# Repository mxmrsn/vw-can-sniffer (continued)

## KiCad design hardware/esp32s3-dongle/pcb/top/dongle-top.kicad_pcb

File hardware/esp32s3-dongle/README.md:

# OBD dongle (v0.4.0, laid out on a temporary outline)

| Path | What it is |
|---|---|
| [`pcb/`](pcb/README.md) | Schematics for both boards and the scripts that generate them |
| [`firmware/`](firmware/README.md) | ESP-IDF firmware: the shared core plus the TJA1043 modes and switching itself off |
| [`docs/architecture.md`](docs/architecture.md) | The two-board stack behind a J1962 plug: partitioning, power and sleep, the board-to-board connector, the mechanical interface with the enclosure, and what is still to verify |

The low-profile version of the [XIAO board](../xiao-esp32s3/README.md): same firmware core, protocol and tools,
plugged straight into the OBD port, and switching itself off when the car is parked. **The schematics are drawn**
and ERC clean, and both boards are routed (0 DRC errors) on a temporary outline, with STEP files for the
enclosure. The real outline follows the enclosure.

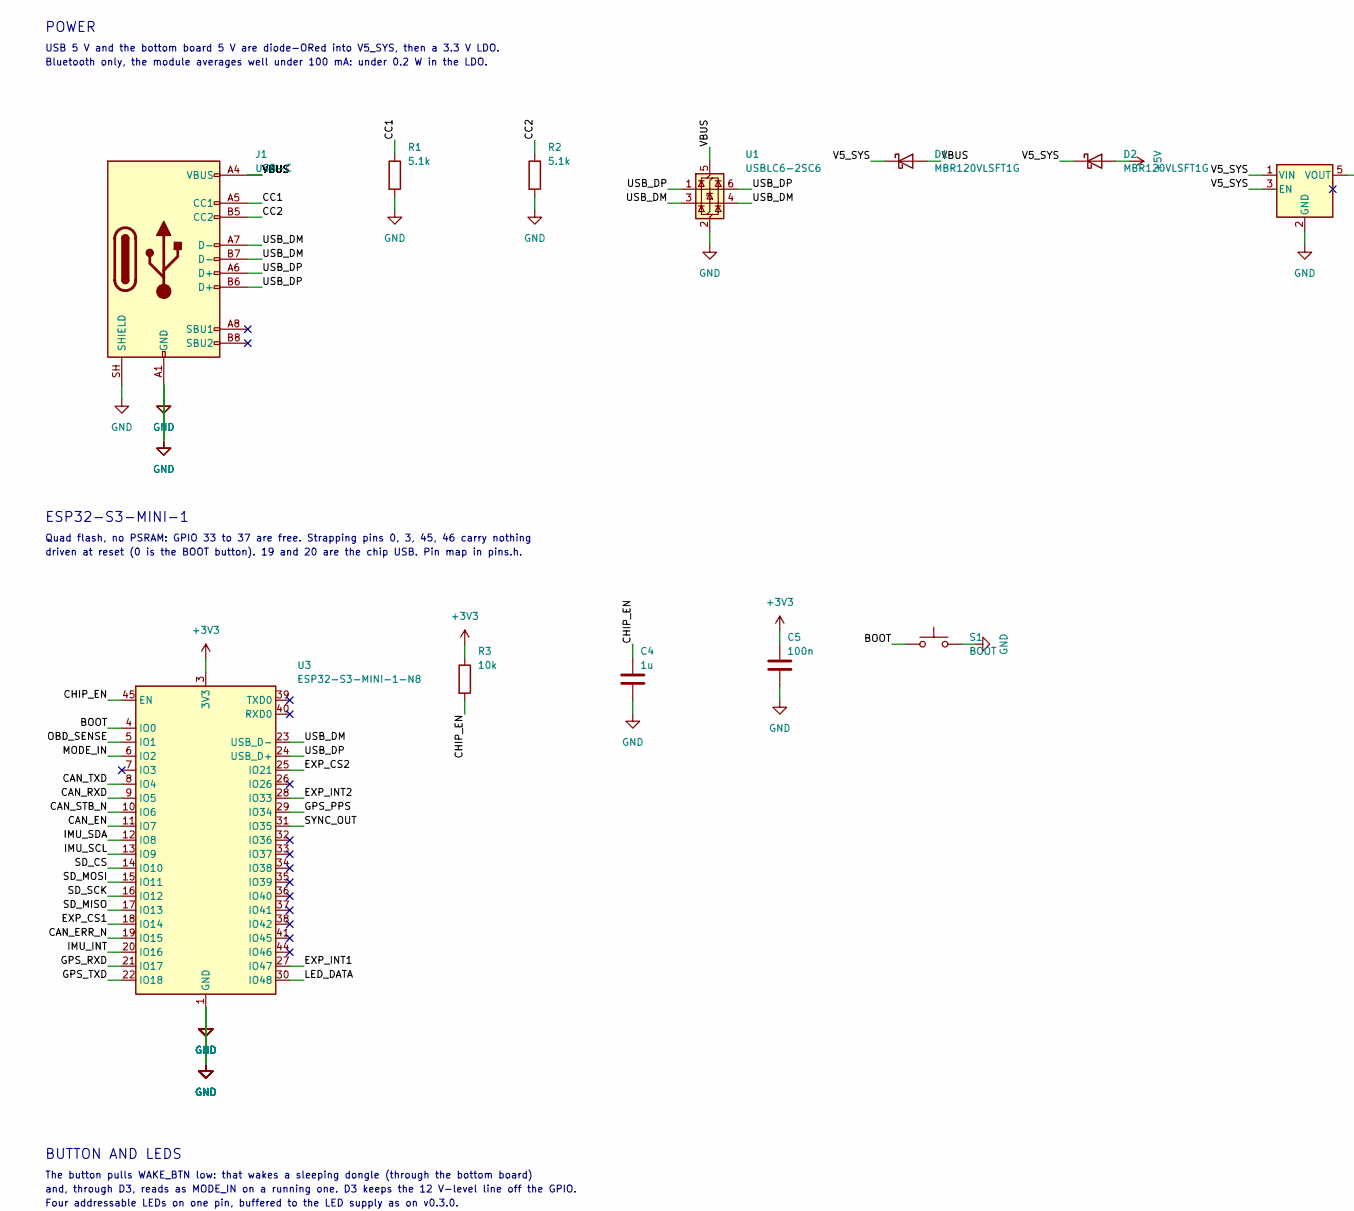
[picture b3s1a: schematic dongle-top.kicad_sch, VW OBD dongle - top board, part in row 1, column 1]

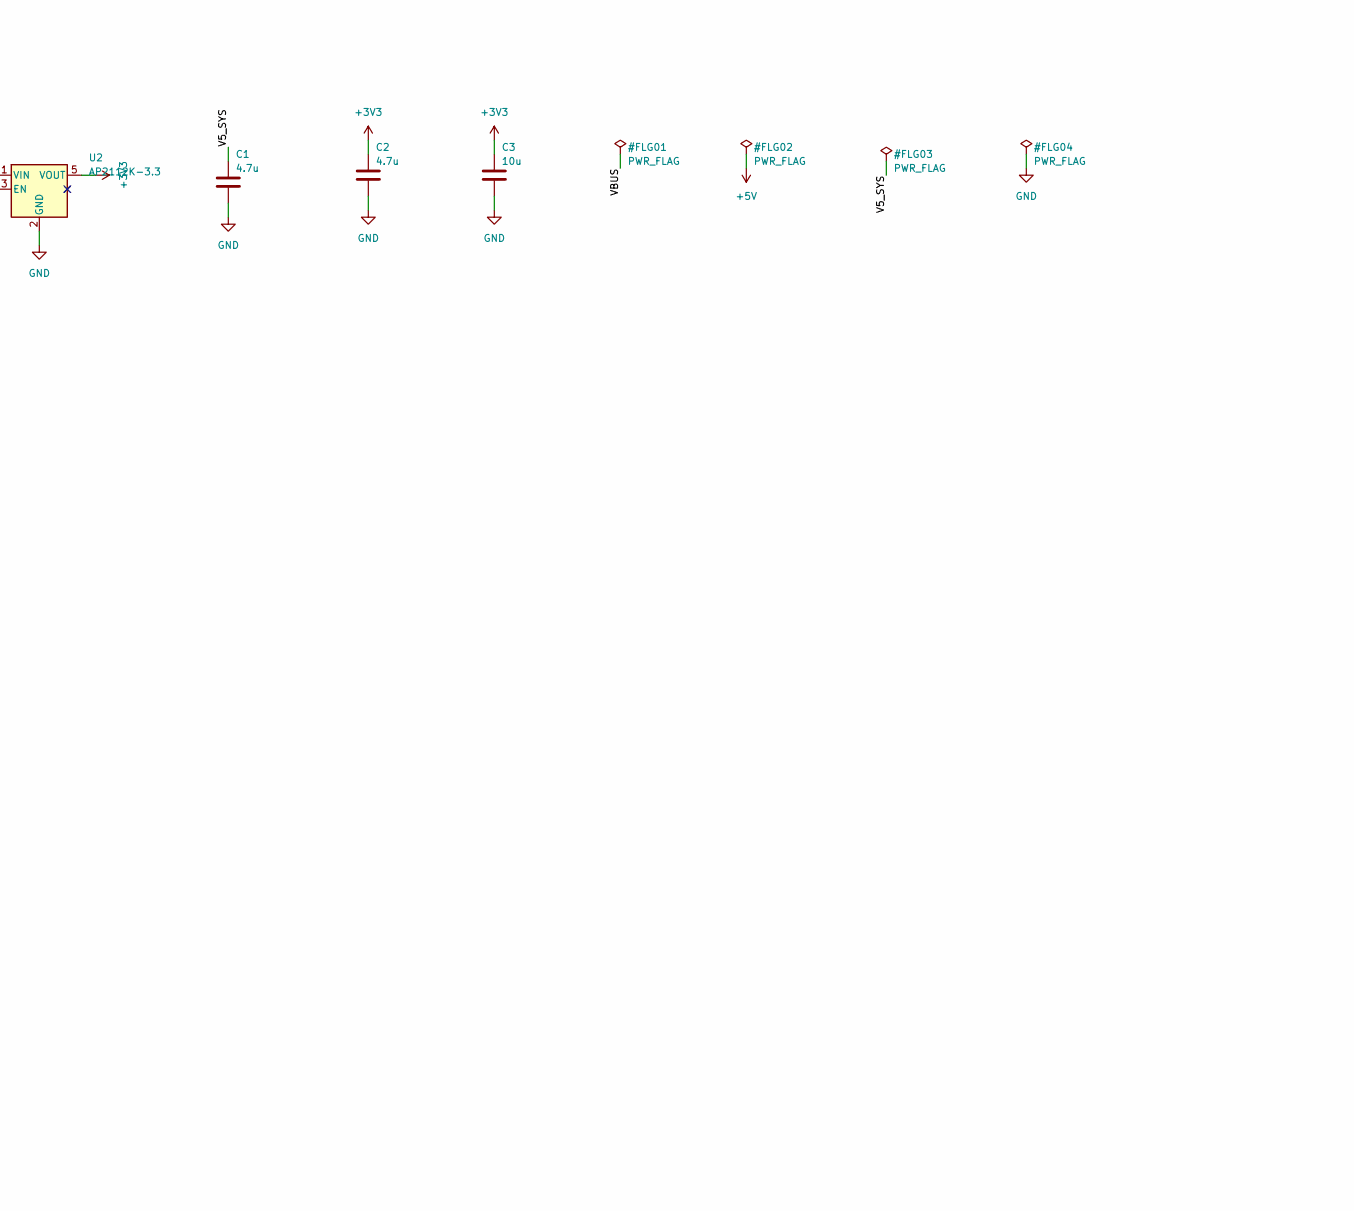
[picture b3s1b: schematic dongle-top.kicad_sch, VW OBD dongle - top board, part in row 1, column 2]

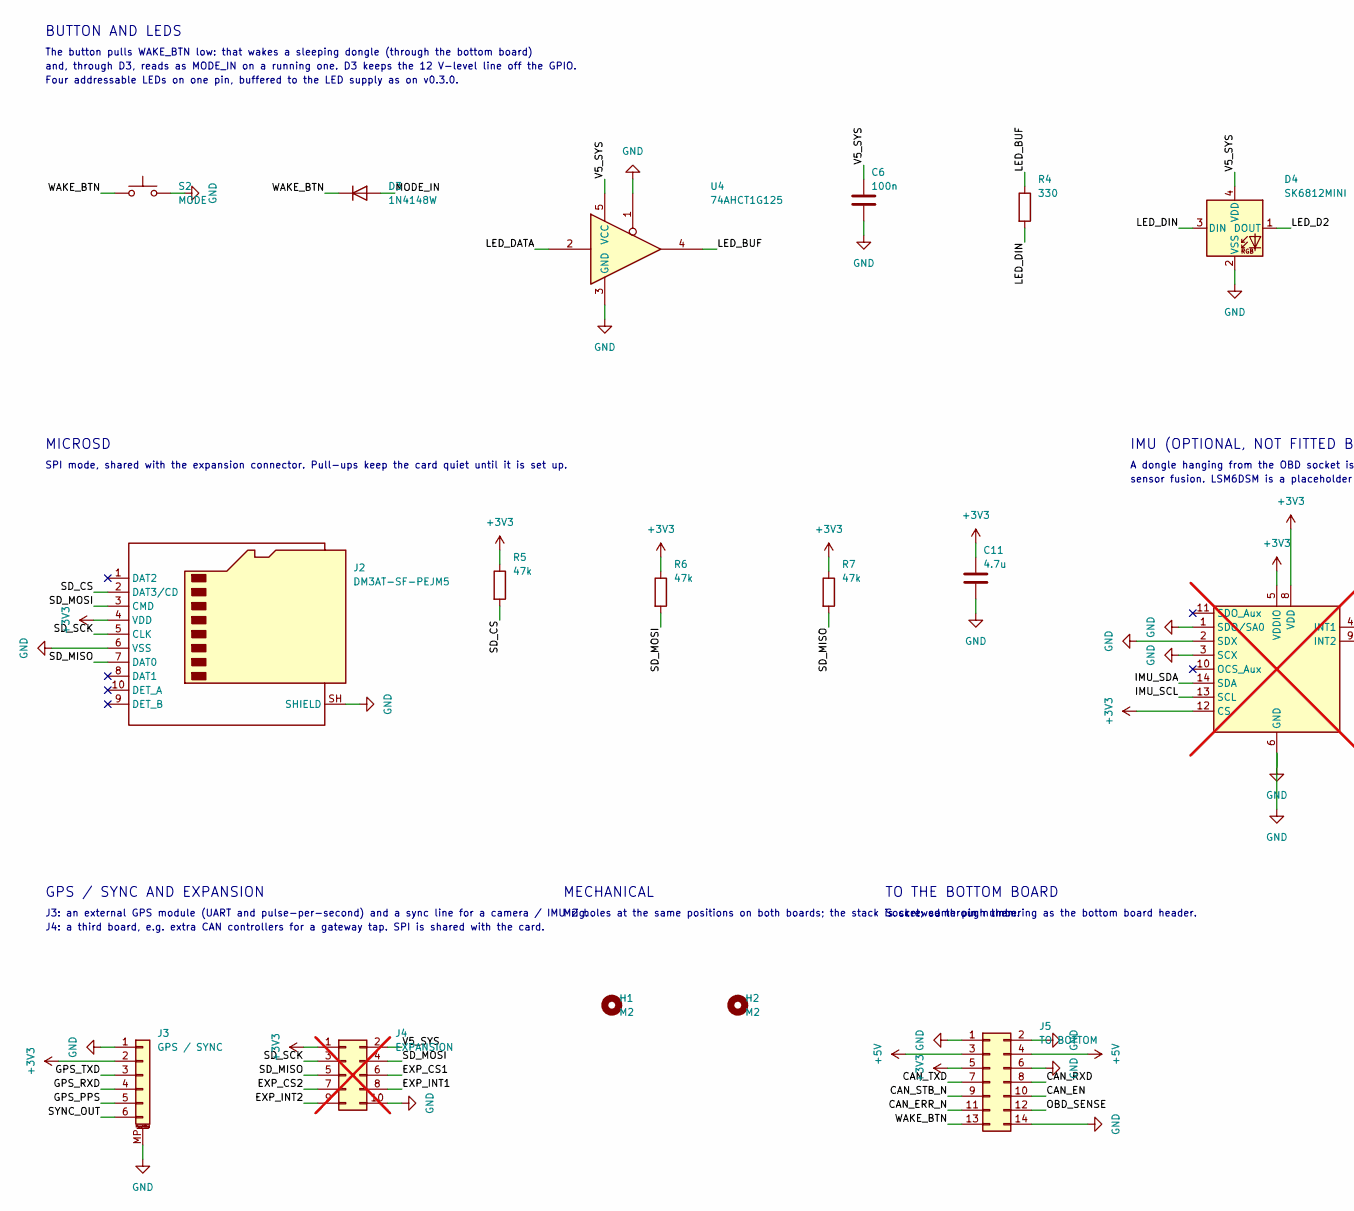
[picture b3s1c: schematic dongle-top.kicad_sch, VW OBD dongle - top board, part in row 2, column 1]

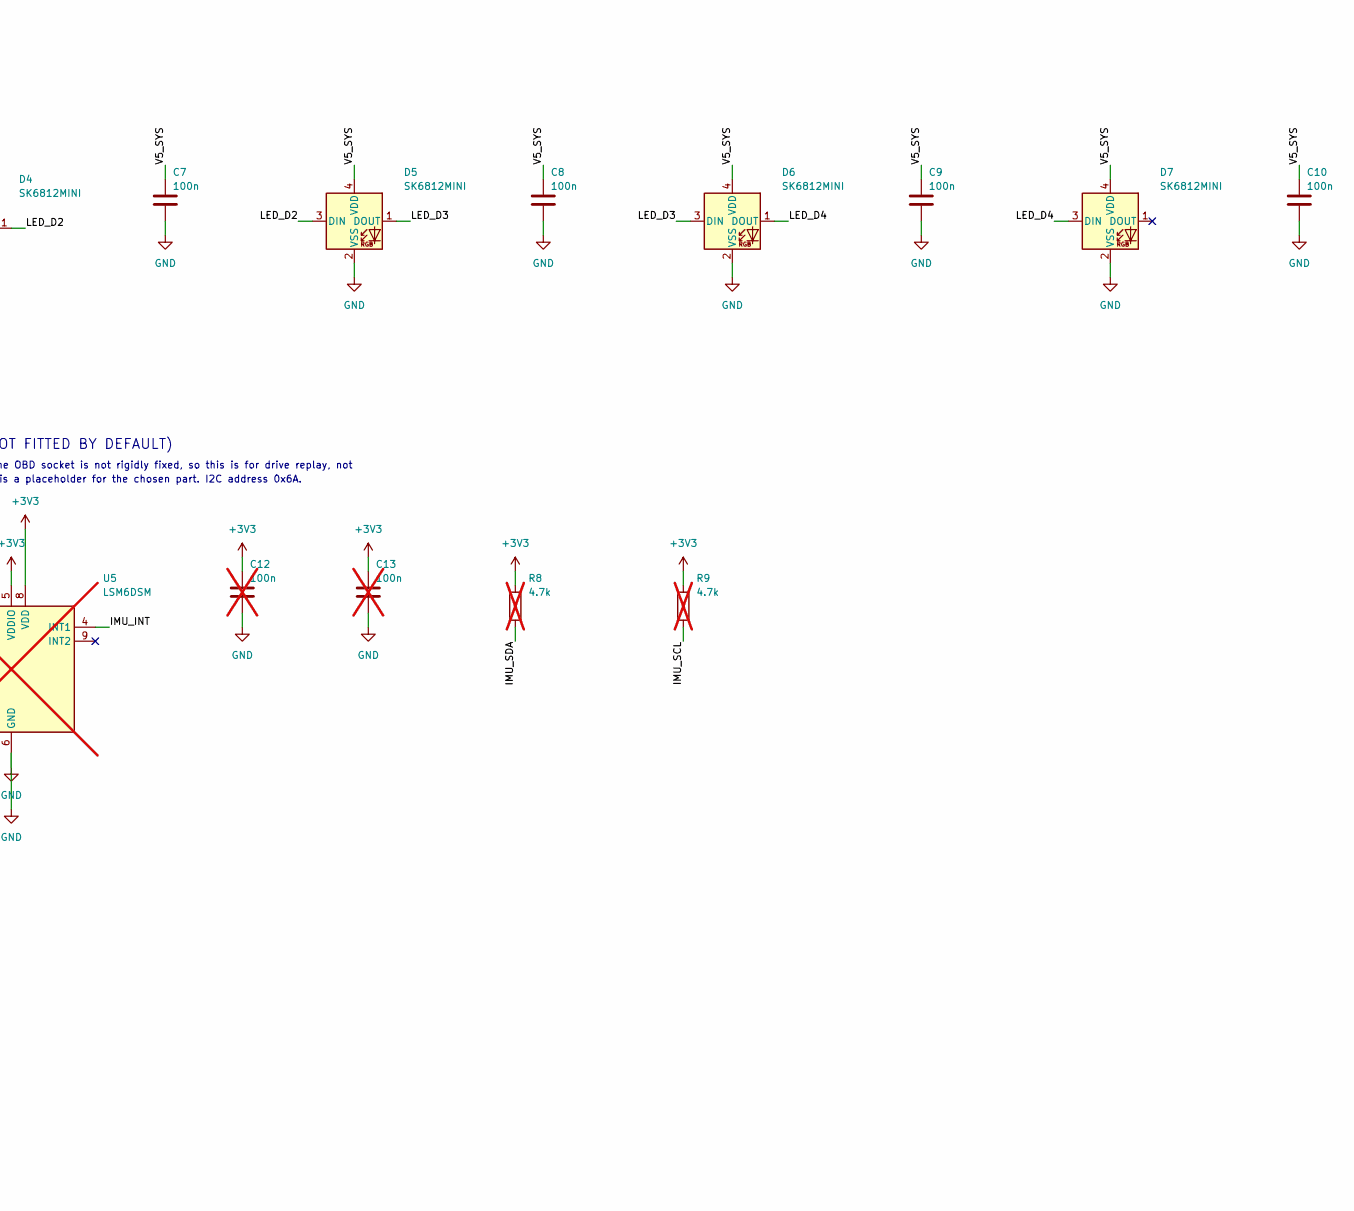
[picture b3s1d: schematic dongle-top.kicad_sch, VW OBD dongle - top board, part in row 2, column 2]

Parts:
C1, C2, C11: 4.7u; C_0603_1608Metric; MPN CC0603KRX5R7BB475; DigiKey 311-1785-1-ND
C3: 10u; C_0805_2012Metric; MPN GMC21X5R106K50NT; DigiKey 4713-GMC21X5R106K50NTCT-ND
C4: 1u; C_0603_1608Metric; MPN CL10A105KB8NNNC
C5, C6, C7, C8, C9, C10: 100n; C_0603_1608Metric; MPN CC0603KRX7R9BB104; DigiKey 311-1344-1-ND
C12, C13: 100n; C_0603_1608Metric; MPN CC0603KRX7R9BB104; DigiKey 311-1344-1-ND; not fitted
D1, D2: MBR120VLSFT1G; D_SOD-123F; MPN MBR120VLSFT1G; DigiKey MBR120VLSFT1GOSCT-ND
D3: 1N4148W; D_SOD-123; MPN 1N4148W-7-F
D4, D5, D6, D7: SK6812MINI; LED_SK6812MINI_PLCC4_3.5x3.5mm_P1.75mm; MPN SK6812MINI (to verify)
H1, H2: M2; MountingHole_2.2mm_M2
J1: USB-C; USB_C_Receptacle_GCT_USB4105-xx-A_16P_TopMnt_Horizontal; MPN USB4105-GF-A
J2: DM3AT-SF-PEJM5; microSD_HC_Hirose_DM3AT-SF-PEJM5; MPN DM3AT-SF-PEJM5; DigiKey HR1964CT-ND
J3: GPS / SYNC; JST_GH_SM06B-GHS-TB_1x06-1MP_P1.25mm_Horizontal; MPN SM06B-GHS-TB(LF)(SN)
J4: EXPANSION; PinHeader_2x05_P1.27mm_Vertical_SMD; not fitted
J5: TO BOTTOM; PinSocket_2x07_P1.27mm_Vertical_SMD
R1, R2: 5.1k; R_0603_1608Metric; MPN CRCW06035K10FKEA
R3: 10k; R_0603_1608Metric; MPN CRCW060310K0FKEA; DigiKey 541-10.0KHCT-ND
R4: 330; R_0603_1608Metric; MPN CRCW0603330RFKEA; DigiKey 541-330HCT-ND
R5, R6, R7: 47k; R_0603_1608Metric; MPN CRCW060347K0FKEA
R8, R9: 4.7k; R_0603_1608Metric; MPN CRCW06034K70FKEA; not fitted
S1: BOOT; SW_SPST_PTS810; MPN PTS810 SJM 250 SMTR LFS
S2: MODE; SW_SPST_PTS810; MPN PTS810 SJM 250 SMTR LFS
U1: USBLC6-2SC6; SOT-23-6; MPN USBLC6-2SC6
U2: AP2112K-3.3; SOT-23-5; MPN AP2112K-3.3TRG1
U3: ESP32-S3-MINI-1-N8; ESP32-S2-MINI-1; MPN ESP32-S3-MINI-1-N8
U4: 74AHCT1G125; SOT-23-5; MPN SN74AHCT1G125DBVR
U5: LSM6DSM; LGA-14_3x2.5mm_P0.5mm_LayoutBorder3x4y; MPN LSM6DSM (placeholder); not fitted

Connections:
+3V3: C2.1, C3.1, C5.1, C11.1, C12.1, C13.1, J2.4 (VDD), J3.2, J4.1, J5.5, R3.1, R5.1, R6.1, R7.1, R8.1, R9.1, U2.5 (VOUT), U3.3 (3V3), U5.5 (VDDIO), U5.8 (VDD), U5.12 (CS)
+5V: D2.2 (A), J5.3, J5.4
/BOOT: S1.1, U3.4 (IO0)
/CAN_EN: J5.10, U3.11 (IO7)
/CAN_ERR_N: J5.11, U3.19 (IO15)
/CAN_RXD: J5.8, U3.9 (IO5)
/CAN_STB_N: J5.9, U3.10 (IO6)
/CAN_TXD: J5.7, U3.8 (IO4)
/CC1: J1.A5 (CC1), R1.1
/CC2: J1.B5 (CC2), R2.1
/CHIP_EN: C4.1, R3.2, U3.45 (EN)
/EXP_CS1: J4.6, U3.18 (IO14)
/EXP_CS2: J4.7, U3.25 (IO21)
/EXP_INT1: J4.8, U3.27 (IO47)
/EXP_INT2: J4.9, U3.28 (IO33)
/GPS_PPS: J3.5, U3.29 (IO34)
/GPS_RXD: J3.4, U3.21 (IO17)
/GPS_TXD: J3.3, U3.22 (IO18)
/IMU_INT: U3.20 (IO16), U5.4 (INT1)
/IMU_SCL: R9.2, U3.13 (IO9), U5.13 (SCL)
/IMU_SDA: R8.2, U3.12 (IO8), U5.14 (SDA)
/LED_BUF: R4.1, U4.4
/LED_D2: D4.1 (DOUT), D5.3 (DIN)
/LED_D3: D5.1 (DOUT), D6.3 (DIN)
/LED_D4: D6.1 (DOUT), D7.3 (DIN)
/LED_DATA: U3.30 (IO48), U4.2
/LED_DIN: D4.3 (DIN), R4.2
/MODE_IN: D3.2 (A), U3.6 (IO2)
/OBD_SENSE: J5.12, U3.5 (IO1)
/SD_CS: J2.2 (DAT3/CD), R5.2, U3.14 (IO10)
/SD_MISO: J2.7 (DAT0), J4.5, R7.2, U3.17 (IO13)
/SD_MOSI: J2.3 (CMD), J4.4, R6.2, U3.15 (IO11)
/SD_SCK: J2.5 (CLK), J4.3, U3.16 (IO12)
/SYNC_OUT: J3.6, U3.31 (IO35)
/USB_DM: J1.A7 (D-), J1.B7 (D-), U1.3 (I/O2), U1.4 (I/O2), U3.23 (USB_D-)
/USB_DP: J1.A6 (D+), J1.B6 (D+), U1.1 (I/O1), U1.6 (I/O1), U3.24 (USB_D+)
/V5_SYS: C1.1, C6.1, C7.1, C8.1, C9.1, C10.1, D1.1 (K), D2.1 (K), D4.4 (VDD), D5.4 (VDD), D6.4 (VDD), D7.4 (VDD), J4.2, U2.1 (VIN), U2.3 (EN), U4.5 (VCC)
/VBUS: D1.2 (A), J1.A4 (VBUS), J1.A9 (VBUS), J1.B4 (VBUS), J1.B9 (VBUS), U1.5 (VBUS)
/WAKE_BTN: D3.1 (K), J5.13, S2.1
GND: C1.2, C2.2, C3.2, C4.2, C5.2, C6.2, C7.2, C8.2, C9.2, C10.2, C11.2, C12.2, C13.2, D4.2 (VSS), D5.2 (VSS), D6.2 (VSS), D7.2 (VSS), J1.A1 (GND), J1.A12 (GND), J1.B1 (GND), J1.B12 (GND), J1.SH (SHIELD), J2.6 (VSS), J2.SH (SHIELD), J3.1, J3.MP (MountPin), J4.10, J5.1, J5.2, J5.6, J5.14, R1.2, R2.2, S1.2, S2.2, U1.2 (GND), U2.2 (GND), U3.1 (GND), U3.2 (GND), U3.42 (GND), U3.43 (GND), U3.46 (GND), U3.47 (GND), U3.48 (GND), U3.49 (GND), U3.50 (GND), U3.51 (GND), U3.52 (GND), U3.53 (GND), U3.54 (GND), U3.55 (GND), U3.56 (GND), U3.57 (GND), U3.58 (GND), U3.59 (GND), U3.60 (GND), U3.61 (GND), U3.62 (GND), U3.63 (GND), U3.64 (GND), U3.65 (GND), U4.1, U4.3 (GND), U5.1 (SDO/SA0), U5.2 (SDX), U5.3 (SCX), U5.6 (GND), U5.7 (GND)

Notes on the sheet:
POWER
USB 5 V and the bottom board 5 V are diode-ORed into V5_SYS, then a 3.3 V LDO.
Bluetooth only, the module averages well under 100 mA: under 0.2 W in the LDO.
ESP32-S3-MINI-1
Quad flash, no PSRAM: GPIO 33 to 37 are free. Strapping pins 0, 3, 45, 46 carry nothing
driven at reset (0 is the BOOT button). 19 and 20 are the chip USB. Pin map in pins.h.
BUTTON AND LEDS
The button pulls WAKE_BTN low: that wakes a sleeping dongle (through the bottom board)
and, through D3, reads as MODE_IN on a running one. D3 keeps the 12 V-level line off the GPIO.
Four addressable LEDs on one pin, buffered to the LED supply as on v0.3.0.
MICROSD
SPI mode, shared with the expansion connector. Pull-ups keep the card quiet until it is set up.
IMU (OPTIONAL, NOT FITTED BY DEFAULT)
A dongle hanging from the OBD socket is not rigidly fixed, so this is for drive replay, not
sensor fusion. LSM6DSM is a placeholder for the chosen part. I2C address 0x6A.
GPS / SYNC AND EXPANSION
J3: an external GPS module (UART and pulse-per-second) and a sync line for a camera / IMU rig.
J4: a third board, e.g. extra CAN controllers for a gateway tap. SPI is shared with the card.
MECHANICAL
M2 holes at the same positions on both boards; the stack is screwed through them.
TO THE BOTTOM BOARD
Socket; same pin numbering as the bottom board header.

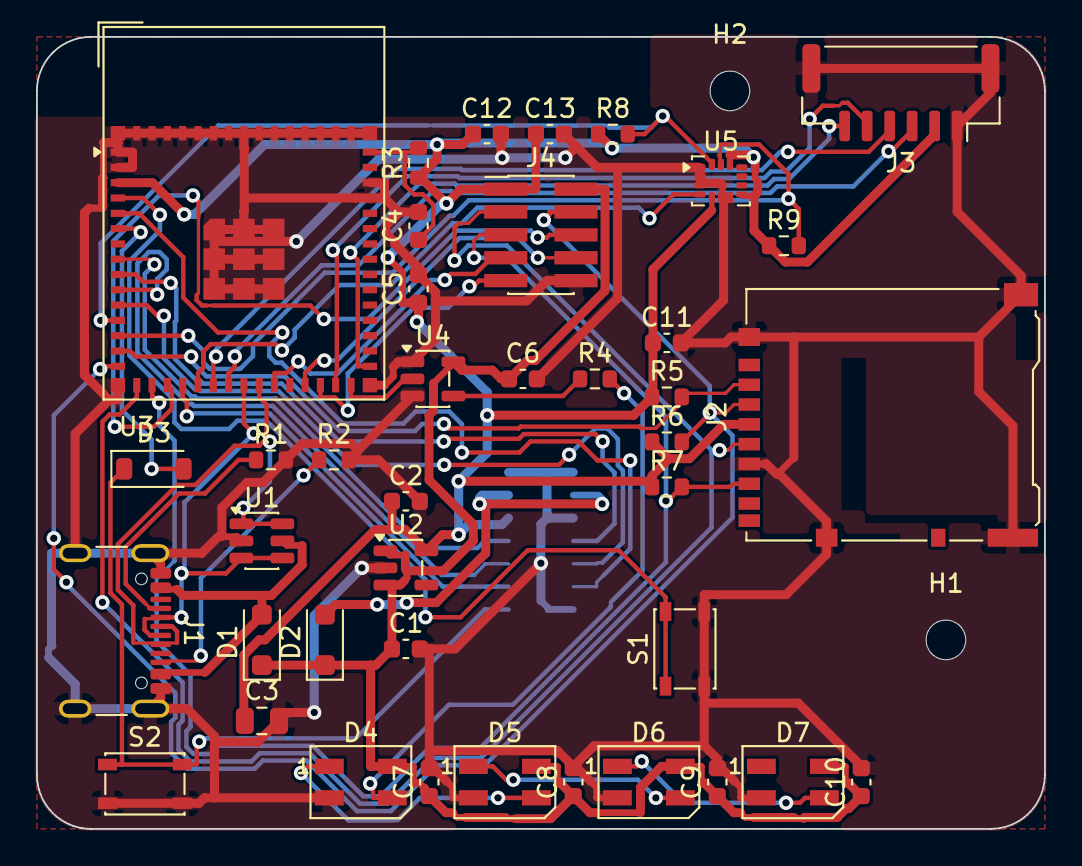
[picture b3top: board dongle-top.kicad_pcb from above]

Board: 2 copper layers, 56.0 x 44.0 mm, 43 parts (1 on the bottom side), 40 nets.

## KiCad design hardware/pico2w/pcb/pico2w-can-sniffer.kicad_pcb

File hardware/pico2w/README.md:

# Pico 2 W diagnostic interface (v0.2.0)

Everything specific to the current board.

| Path | What it is |
|---|---|
| [`pcb/`](pcb/docs/README.md) | KiCad project, with the board write-up in `pcb/docs/README.md` |
| `pcb/bom/` | Purchase BOM with DigiKey part numbers, and a cart-upload file |
| `pcb/fab/` | Gerbers, drill files and placement file |
| [`pcb/spice/`](pcb/spice/README.md) | Regulator power-stage simulation |
| [`pcb/3dmodels/`](pcb/3dmodels/README.md) | 3D models not in the stock KiCad library |
| [`firmware/`](firmware/README.md) | Pico 2 W firmware, host simulator (`firmware/sim/`) and protocol tests (`firmware/tests/`) |
| [`docs/bringup_plan.md`](docs/bringup_plan.md) | What to test, in order, when the hardware arrives |
| [`docs/logging.md`](docs/logging.md) | Logging to the microSD card, with or without a computer attached |
| [`docs/link_protocol.md`](docs/link_protocol.md) | The packet protocol an app uses, and the Bluetooth LE plan |

The host tools that drive this board are board-independent and live in [`../../tools/vwdiag`](../../tools/vwdiag/README.md).

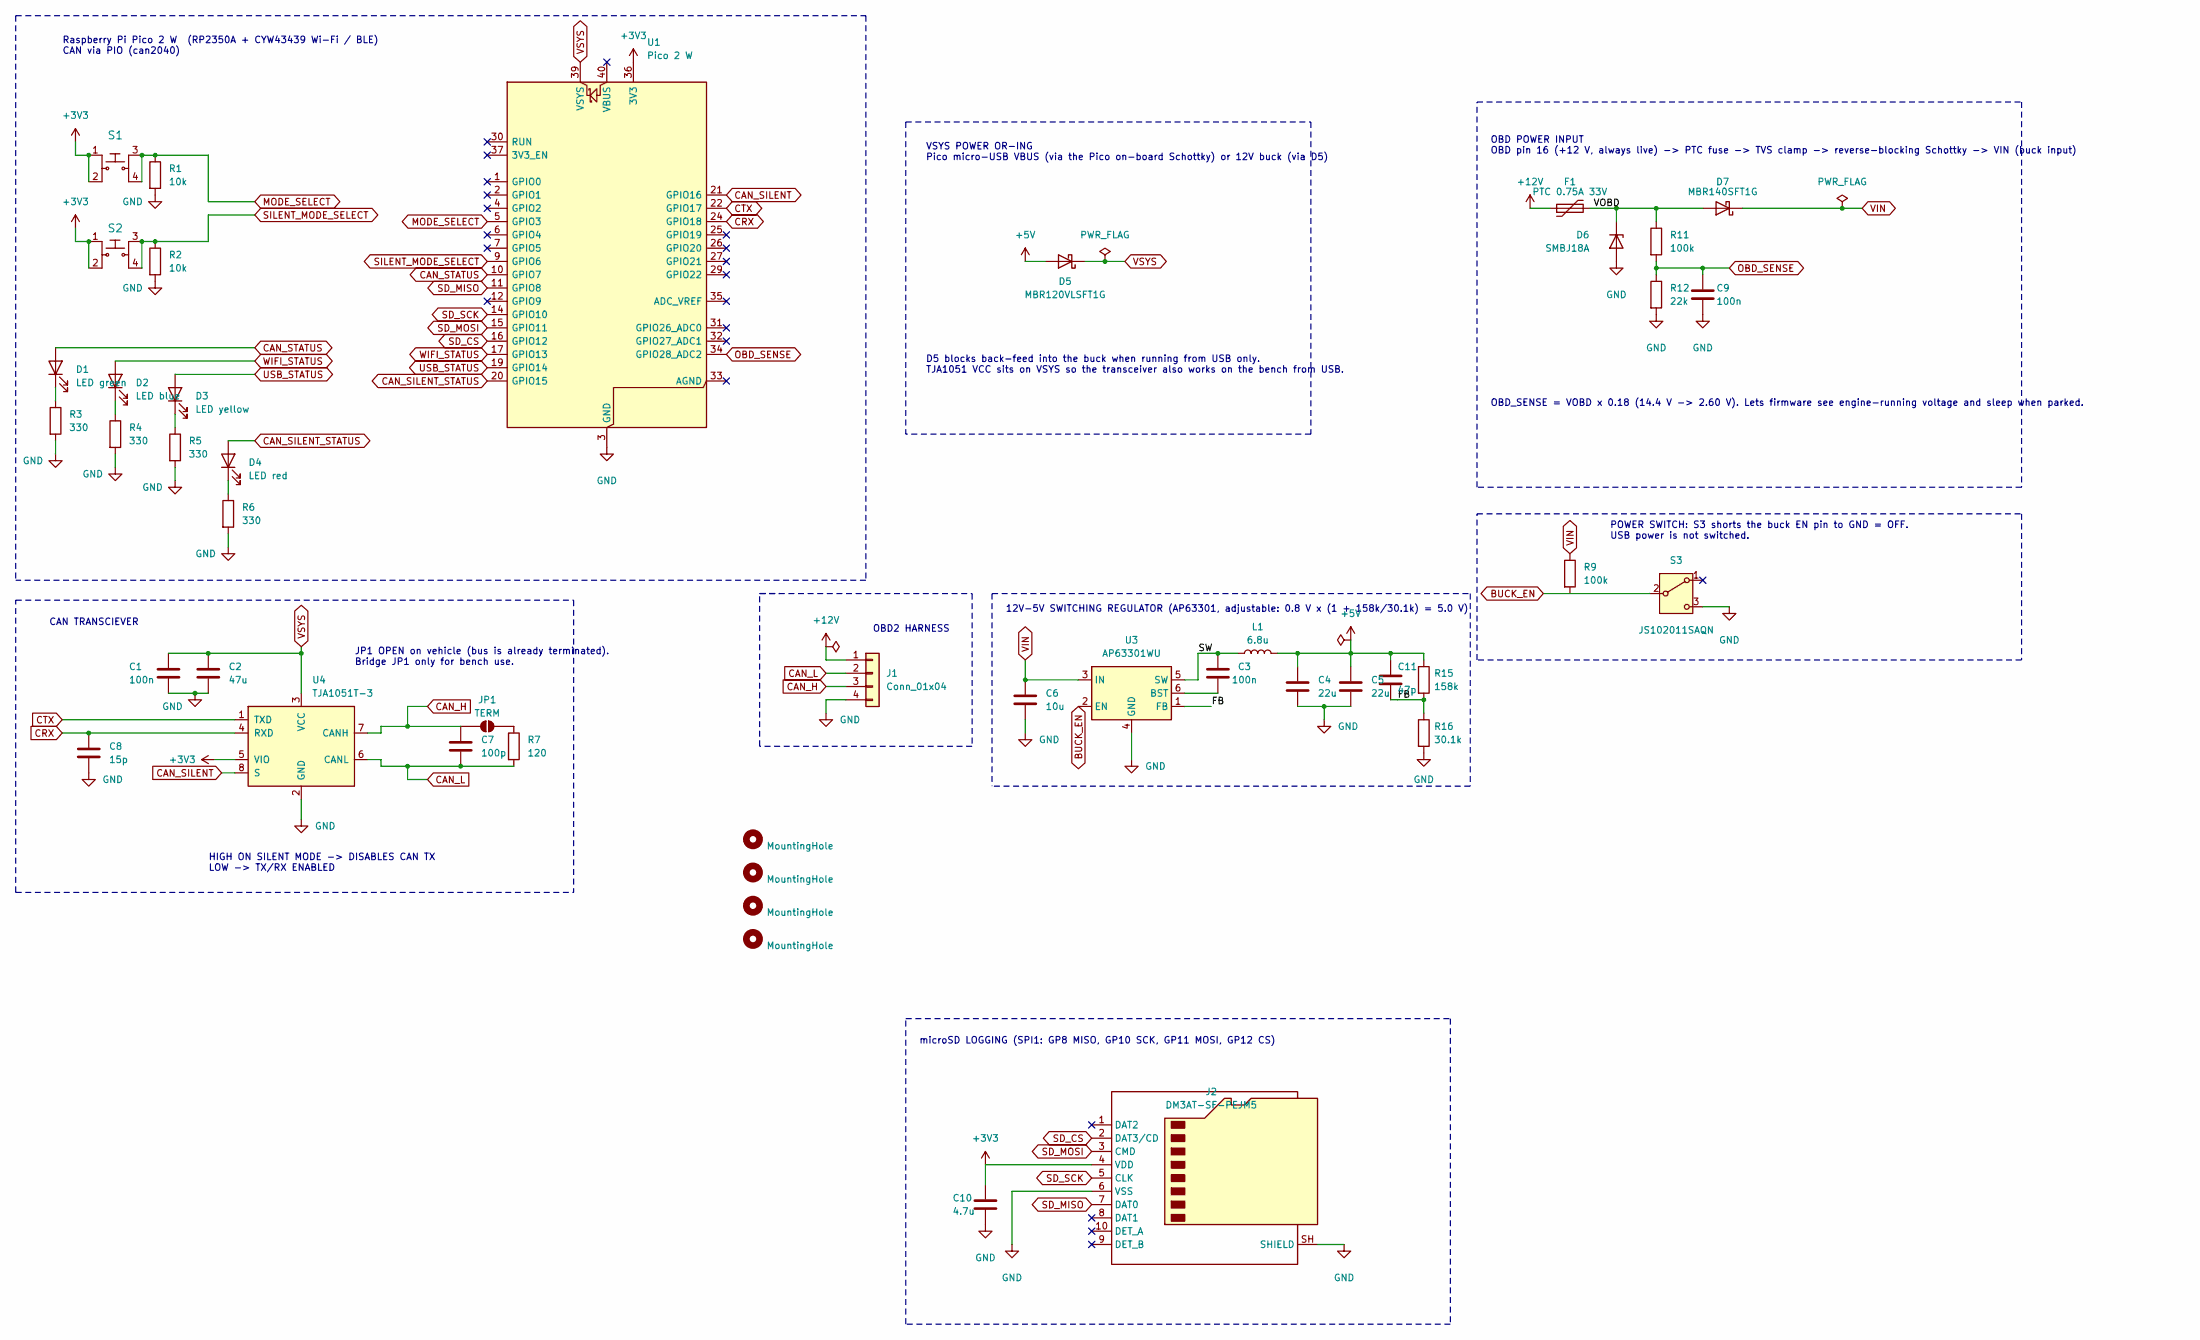
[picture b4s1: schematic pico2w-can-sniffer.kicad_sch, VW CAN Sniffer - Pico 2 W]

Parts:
C1, C3: 100n; C_0805_2012Metric; MPN CL21B104KBCNNNC; DigiKey 1276-1003-1-ND
C2: 47u; C_0805_2012Metric; MPN CL21A476MQCLRNC; DigiKey 1276-2420-1-ND
C4, C5: 22u; C_0805_2012Metric; MPN CL21A226KOQNNNE; DigiKey 1276-6526-1-ND
C6: 10u; C_0805_2012Metric; MPN GMC21X5R106K50NT; DigiKey 4713-GMC21X5R106K50NTCT-ND
C7: 100p; C_0805_2012Metric; MPN CL21C101JBANNNC; DigiKey 1276-1014-1-ND
C8: 15p; C_0805_2012Metric; MPN CC0805JRNPO9BN150; DigiKey 311-1101-1-ND
C9: 100n; C_0603_1608Metric; MPN CC0603KRX7R9BB104; DigiKey 311-1344-1-ND
C10: 4.7u; C_0603_1608Metric; MPN CC0603KRX5R7BB475; DigiKey 311-1785-1-ND
C11: 47p; C_0603_1608Metric; MPN CL10C470JB8NNNC; DigiKey 1276-1037-1-ND
D1: LED green; LED_0603_1608Metric; MPN LTST-C191KGKT; DigiKey 160-1446-1-ND
D2: LED blue; LED_0603_1608Metric; MPN LTST-C191TBKT; DigiKey 160-1647-1-ND
D3: LED yellow; LED_0603_1608Metric; MPN LTST-C191KSKT; DigiKey 160-1448-1-ND
D4: LED red; LED_0603_1608Metric; MPN LTST-C191KRKT; DigiKey 160-1447-1-ND
D5: MBR120VLSFT1G; D_SOD-123F; MPN MBR120VLSFT1G; DigiKey MBR120VLSFT1GOSCT-ND
D6: SMBJ18A; D_SMB; MPN SMBJ18A; DigiKey SMBJ18ALFCT-ND
D7: MBR140SFT1G; D_SOD-123F; MPN MBR140SFT1G; DigiKey MBR140SFT1GOSCT-ND
F1: PTC 0.75A 33V; Fuse_1812_4532Metric; MPN 1812L075/33DR; DigiKey F3355CT-ND
H1, H2, H3, H4: MountingHole; MountingHole_2.5mm
J1: Conn_01x04; CONN_874370231-SD_04_MOL; MPN 0874370473; DigiKey WM3969CT-ND
J2: DM3AT-SF-PEJM5; microSD_HC_Hirose_DM3AT-SF-PEJM5; MPN DM3AT-SF-PEJM5; DigiKey HR1964CT-ND
JP1: TERM; SolderJumper-2_P1.3mm_Open_RoundedPad1.0x1.5mm
L1: 6.8u; L_Wurth_WE-LQSH-4020; MPN 74404042068; DigiKey 732-5507-1-ND
R1, R2: 10k; R_0603_1608Metric; MPN CRCW060310K0FKEA; DigiKey 541-10.0KHCT-ND
R3, R4, R5, R6: 330; R_0603_1608Metric; MPN CRCW0603330RFKEA; DigiKey 541-330HCT-ND
R7: 120; R_0603_1608Metric; MPN RC0603FR-07120RL; DigiKey 311-120HRCT-ND
R9, R11: 100k; R_0603_1608Metric; MPN CRCW0603100KFKEA; DigiKey 541-100KHCT-ND
R12: 22k; R_0603_1608Metric; MPN CRCW060322K0FKEA; DigiKey 541-22.0KHCT-ND
R15: 158k; R_0603_1608Metric; MPN CRCW0603158KFKEA; DigiKey 541-158KHCT-ND
R16: 30.1k; R_0603_1608Metric; MPN CRCW060330K1FKEA; DigiKey 541-30.1KHCT-ND
S1, S2: PTS645SM43SMTR92_LFS; Switch_Tactile_SMD_6x6mm_PTS645; MPN PTS645SM43SMTR92 LFS; Digi-Key_PN CKN9112CT-ND
S3: JS102011SAQN; SW_SPDT_CK_JS102011SAQN; MPN JS102011SAQN; DigiKey 401-1999-1-ND
U1: Pico 2 W; RaspberryPi_Pico_Common_THT; MPN RP2350-PICO2-W; DigiKey 1188-RP2350-PICO2-W-ND
U3: AP63301WU; TSOT-23-6; MPN AP63301WU-7; DigiKey 31-AP63301WU-7CT-ND
U4: TJA1051T-3; SOIC-8_3.9x4.9mm_P1.27mm; MPN TJA1051T/3,118; DigiKey 568-8684-1-ND

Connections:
+3V3: C10.1, J2.4 (VDD), S1.1, S1.2, S2.1, S2.2, U1.36 (3V3), U4.5 (VIO)
+5V: C4.1, C5.1, C11.1, D5.2 (A), L1.2, R15.1
+12V: F1.1, J1.1
/FB: C11.2, R15.2, R16.1, U3.1 (FB)
/SW: C3.2, L1.1, U3.5 (SW)
/VOBD: D6.1 (K), D7.2 (A), F1.2, R11.1
BUCK_EN: R9.2, S3.2 (B), U3.2 (EN)
CAN_H: C7.1, J1.3, JP1.1 (A), U4.7 (CANH)
CAN_L: C7.2, J1.2, R7.2, U4.6 (CANL)
CAN_SILENT: U1.21 (GPIO16), U4.8 (S)
CAN_SILENT_STATUS: D4.2 (A), U1.20 (GPIO15)
CAN_STATUS: D1.2 (A), U1.10 (GPIO7)
CRX: C8.1, U1.24 (GPIO18), U4.4 (RXD)
CTX: U1.22 (GPIO17), U4.1 (TXD)
GND: C1.2, C2.2, C4.2, C5.2, C6.2, C8.2, C9.2, C10.2, D6.2 (A), J1.4, J2.6 (VSS), J2.SH (SHIELD), R1.2, R2.2, R3.2, R4.2, R5.2, R6.2, R12.2, R16.2, S3.3 (C), U1.3 (GND), U1.8 (GND), U1.13 (GND), U1.18 (GND), U1.23 (GND), U1.28 (GND), U1.38 (GND), U3.4 (GND), U4.2 (GND)
MODE_SELECT: R1.1, S1.3, S1.4, U1.5 (GPIO3)
unnamed: D1.1 (K), R3.1
unnamed: D2.1 (K), R4.1
unnamed: D3.1 (K), R5.1
unnamed: D4.1 (K), R6.1
unnamed: JP1.2 (B), R7.1
unnamed: C3.1, U3.6 (BST)
OBD_SENSE: C9.1, R11.2, R12.1, U1.34 (GPIO28_ADC2)
SD_CS: J2.2 (DAT3/CD), U1.16 (GPIO12)
SD_MISO: J2.7 (DAT0), U1.11 (GPIO8)
SD_MOSI: J2.3 (CMD), U1.15 (GPIO11)
SD_SCK: J2.5 (CLK), U1.14 (GPIO10)
SILENT_MODE_SELECT: R2.1, S2.3, S2.4, U1.9 (GPIO6)
USB_STATUS: D3.2 (A), U1.19 (GPIO14)
VIN: C6.1, D7.1 (K), R9.1, U3.3 (IN)
VSYS: C1.1, C2.1, D5.1 (K), U1.39 (VSYS), U4.3 (VCC)
WIFI_STATUS: D2.2 (A), U1.17 (GPIO13)

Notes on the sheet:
Raspberry Pi Pico 2 W (RP2350A + CYW43439 Wi-Fi / BLE) CAN via PIO (can2040)
12V-5V SWITCHING REGULATOR (AP63301, adjustable: 0.8 V x (1 + 158k/30.1k) = 5.0 V)
CAN TRANSCIEVER
HIGH ON SILENT MODE -> DISABLES CAN TX LOW -> TX/RX ENABLED
OBD2 HARNESS
VSYS POWER OR-ING Pico micro-USB VBUS (via the Pico on-board Schottky) or 12V buck (via D5)
D5 blocks back-feed into the buck when running from USB only. TJA1051 VCC sits on VSYS so the transceiver also works on the bench from USB.
JP1 OPEN on vehicle (bus is already terminated). Bridge JP1 only for bench use.
OBD POWER INPUT OBD pin 16 (+12 V, always live) -> PTC fuse -> TVS clamp -> reverse-blocking Schottky -> VIN (buck input)
OBD_SENSE = VOBD x 0.18 (14.4 V -> 2.60 V). Lets firmware see engine-running voltage and sleep when parked.
POWER SWITCH: S3 shorts the buck EN pin to GND = OFF. USB power is not switched.
microSD LOGGING (SPI1: GP8 MISO, GP10 SCK, GP11 MOSI, GP12 CS)

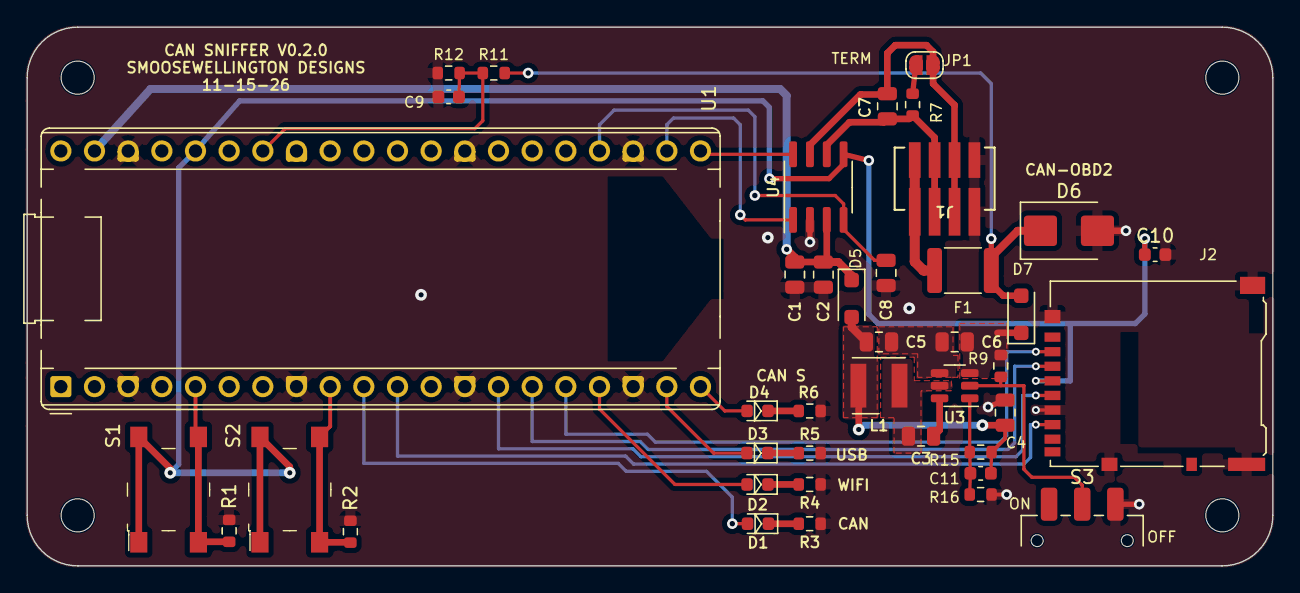
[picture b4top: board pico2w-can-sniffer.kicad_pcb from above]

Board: 2 copper layers, 94.0 x 40.6 mm, 45 parts (0 on the bottom side), 32 nets.

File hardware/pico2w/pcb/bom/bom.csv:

Refs,Qty,Value,Description,Manufacturer,MPN,DigiKey PN,DigiKey stock (2026-11-15),Unit price USD (qty 1),Notes
"C1,C3",2,100n,Cap cer 0.1uF 50V X7R 0805,Samsung Electro-Mechanics,CL21B104KBCNNNC,1276-1003-1-ND,"3,797,498",0.10,
C2,1,47u,Cap cer 47uF 6.3V X5R 0805,Samsung Electro-Mechanics,CL21A476MQCLRNC,1276-2420-1-ND,"6,613",0.53,6.3 V part on the ~5 V VSYS rail; 10 V versions were all out of stock
"C4,C5",2,22u,Cap cer 22uF 16V X5R 0805,Samsung Electro-Mechanics,CL21A226KOQNNNE,1276-6526-1-ND,"95,660",0.42,Buck output
C6,1,10u,Cap cer 10uF 50V X5R 0805,Cal-Chip Electronics,GMC21X5R106K50NT,4713-GMC21X5R106K50NTCT-ND,"15,332",1.76,Buck input; 50 V for OBD transients. Only in-stock 50 V option
C7,1,100p,Cap cer 100pF 50V C0G 0805,Samsung Electro-Mechanics,CL21C101JBANNNC,1276-1014-1-ND,"127,138",0.10,
C8,1,15p,Cap cer 15pF 50V C0G 0805,YAGEO,CC0805JRNPO9BN150,311-1101-1-ND,"31,676",,
C9,1,100n,Cap cer 0.1uF 50V X7R 0603,YAGEO,CC0603KRX7R9BB104,311-1344-1-ND,"3,118,948",,
C10,1,4.7u,Cap cer 4.7uF 16V X5R 0603,YAGEO,CC0603KRX5R7BB475,311-1785-1-ND,"125,573",,
C11,1,47p,Cap cer 47pF 50V C0G 0603,Samsung Electro-Mechanics,CL10C470JB8NNNC,1276-1037-1-ND,"1,223,201",,Feed-forward capacitor
D1,1,LED green,LED green 0603,Lite-On,LTST-C191KGKT,160-1446-1-ND,"2,222,101",,CAN activity
D2,1,LED blue,LED blue 0603,Lite-On,LTST-C191TBKT,160-1647-1-ND,"276,079",,Wi-Fi; will be dim on 330R at 3.3 V
D3,1,LED yellow,LED yellow 0603,Lite-On,LTST-C191KSKT,160-1448-1-ND,"724,486",0.16,USB
D4,1,LED red,LED red 0603,Lite-On,LTST-C191KRKT,160-1447-1-ND,"1,314,623",0.15,Silent mode
D5,1,MBR120VLSFT1G,Schottky 20V 1A SOD-123FL,onsemi,MBR120VLSFT1G,MBR120VLSFT1GOSCT-ND,"105,067",0.61,
D6,1,SMBJ18A,TVS 18V 29.2Vc unidirectional SMB,Littelfuse,SMBJ18A,SMBJ18ALFCT-ND,"26,211",,
D7,1,MBR140SFT1G,Schottky 40V 1A SOD-123FL,onsemi,MBR140SFT1G,MBR140SFT1GOSCT-ND,"49,072",0.60,
F1,1,PTC 0.75A 33V,PTC resettable fuse 33V 750mA 1812,Littelfuse,1812L075/33DR,F3355CT-ND,"18,996",,
J1,1,Pico-SPOX 4-pin,Header 4 pos 1.5mm vertical SMD,Molex,0874370473,WM3969CT-ND,"18,264",0.94,Mating housing and crimps not included
J2,1,DM3AT-SF-PEJM5,microSD push-push socket,Hirose,DM3AT-SF-PEJM5,HR1964CT-ND,"72,391",3.55,
L1,1,6.8u,Inductor 6.8uH 1.45A 4x4x1.8mm WE-LQS 4020,Wurth Elektronik,74404042068,732-5507-1-ND,88,1.16,Low stock. Check the land pattern against the footprint before ordering
"R1,R2",2,10k,Res 10k 1% 1/10W 0603,Vishay Dale,CRCW060310K0FKEA,541-10.0KHCT-ND,"2,848,541",,
"R3,R4,R5,R6",4,330,Res 330R 1% 1/10W 0603,Vishay Dale,CRCW0603330RFKEA,541-330HCT-ND,"313,586",,
R7,1,120,Res 120R 1% 1/10W 0603,YAGEO,RC0603FR-07120RL,311-120HRCT-ND,"4,590",0.10,
"R9,R11",2,100k,Res 100k 1% 1/10W 0603,Vishay Dale,CRCW0603100KFKEA,541-100KHCT-ND,"2,913,990",,
R12,1,22k,Res 22k 1% 1/10W 0603,Vishay Dale,CRCW060322K0FKEA,541-22.0KHCT-ND,"282,701",,
R15,1,158k,Res 158k 1% 1/10W 0603,Vishay Dale,CRCW0603158KFKEA,541-158KHCT-ND,"20,675",,"Feedback divider, top"
R16,1,30.1k,Res 30.1k 1% 1/10W 0603,Vishay Dale,CRCW060330K1FKEA,541-30.1KHCT-ND,"90,123",,"Feedback divider, bottom"
"S1,S2",2,PTS645SM43SMTR92 LFS,Tactile switch 6x6mm SMD,C&K,PTS645SM43SMTR92 LFS,CKN9112CT-ND,"127,640",,
S3,1,JS102011SAQN,Slide switch SPDT right-angle SMD,C&K,JS102011SAQN,401-1999-1-ND,"52,303",0.90,
U1,1,Pico 2 W,"Raspberry Pi Pico 2 W (RP2350), sold by Olimex, no headers",Olimex,RP2350-PICO2-W,1188-RP2350-PICO2-W-ND,2,10.09,"Only 2 in stock. Raspberry Pi's own listing (SC1633, 2648-SC1633CT-ND) showed 0"
U3,1,AP63301WU,Buck regulator adjustable 3A TSOT-26,Diodes Incorporated,AP63301WU-7,31-AP63301WU-7CT-ND,156,0.96,"Low stock. Automotive AP63301QWU-7 (31-AP63301QWU-7CT-ND, 815 in stock) is a drop-in"
U4,1,TJA1051T/3,CAN transceiver SO-8 with VIO,NXP,"TJA1051T/3,118",568-8684-1-ND,"12,998",,
--,2,Socket strip,"Socket 1x20 2.54mm, on the board for the Pico",Sullins,PPTC201LFBN-RC,S7018-ND,"17,802",1.14,Not on schematic
--,2,Pin header,"Header 1x20 2.54mm, soldered to the Pico",Sullins,PRPC020SAAN-RC,35-PRPC020SAAN-RC-ND,"64,801",0.38,Not on schematic; the Olimex Pico has no headers

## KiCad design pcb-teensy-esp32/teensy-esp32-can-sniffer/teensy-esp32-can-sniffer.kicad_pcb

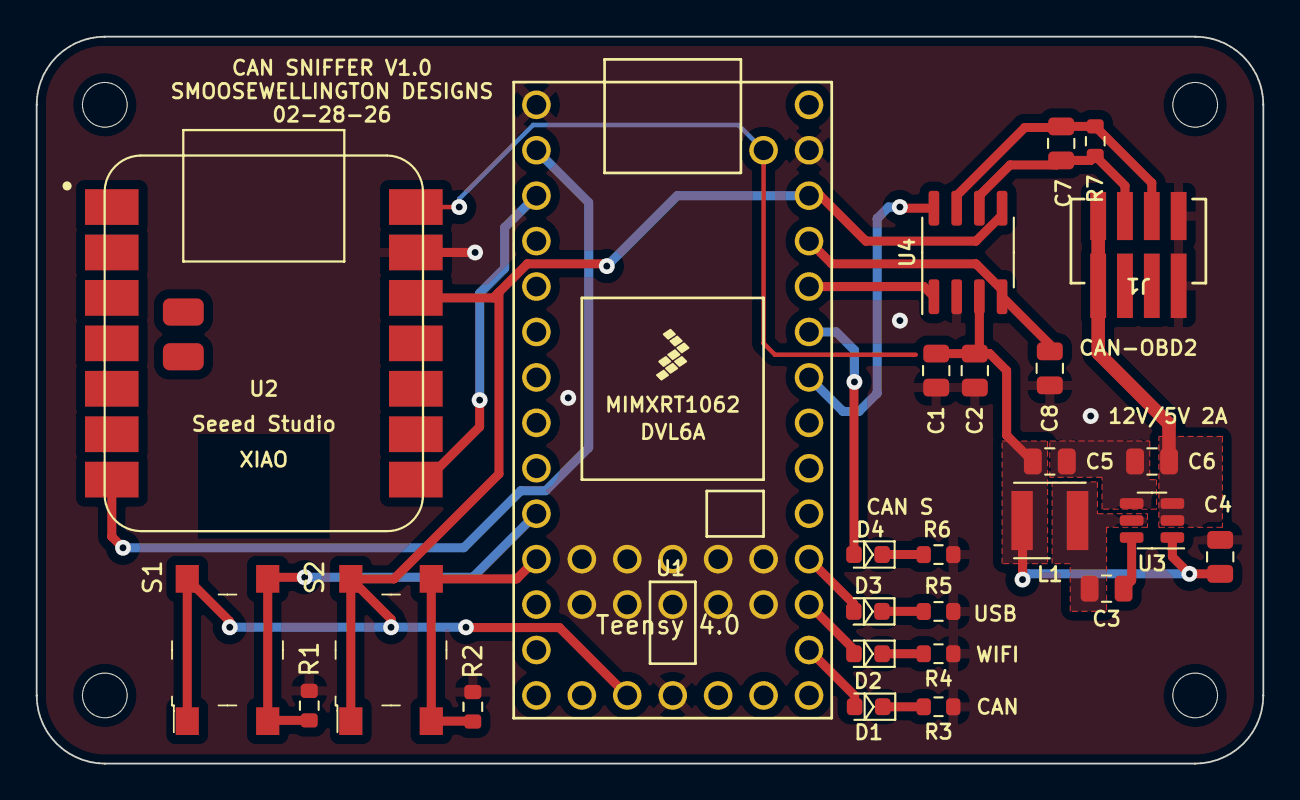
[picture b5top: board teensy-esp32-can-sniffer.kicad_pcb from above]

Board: 2 copper layers, 68.6 x 40.6 mm, 31 parts (0 on the bottom side), 23 nets.

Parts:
C1, C3: 100n; C_0805_2012Metric
C2: 47u; C_0805_2012Metric
C4, C5: 22u; C_0805_2012Metric
C6: 10u; C_0805_2012Metric
C7: 100p; C_0805_2012Metric
C8: 15p; C_0805_2012Metric
D1, D2, D3, D4: LED; LED_0603_1608Metric
H1, H2, H3, H4: MountingHole; MountingHole_2.5mm
J1: Conn_01x04; CONN_874370231-SD_04_MOL
L1: 4.7u; L_Wurth_WE-LQSH-4020
R1, R2: 10k; R_0603_1608Metric
R3, R4, R5, R6: 330; R_0603_1608Metric
R7: 120; R_0603_1608Metric
S1, S2: PTS645SM43SMTR92_LFS; Switch_Tactile_SMD_6x6mm_PTS645
U1: Teensy4.0; Teensy40
U2: Seeed_Studio_XIAO_ESP32S3; XIAO-ESP32S3
U3: AP63205WU; TSOT-23-6
U4: TJA1051T-3; SOIC-8_3.9x4.9mm_P1.27mm

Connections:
+3V3: S1.1, S1.2, S2.1, S2.2, U1.16 (3V3), U1.31 (3V3), U2.12 (3V3), U4.5 (VIO)
+5V: C1.1, C2.1, C4.1, C5.1, L1.2, U1.33 (VIN), U1.34 (VUSB), U2.14 (5V), U3.1 (FB), U4.3 (VCC)
+12V: C6.1, J1.1, U3.2 (EN), U3.3 (IN)
/BUTTON_MODE: R1.1, S1.3, S1.4, U1.10 (8_TX2_IN1)
/BUTTON_SELECT: R2.1, S2.3, S2.4, U1.11 (9_OUT1C)
/CAN_HEARTBEAT: D1.2 (A), U1.21 (14_A0_TX3_SPDIF_OUT)
/CAN_SILENT_STATUS: D4.2 (A), U1.28 (21_A7_RX5_BCLK1)
/SW: C3.2, L1.1, U3.5 (SW)
/USB_HEARTBEAT: D3.2 (A), U1.23 (16_A2_RX4_SCL1)
/WIFI_HEARTBEAT: D2.2 (A), U1.22 (15_A1_RX3_SPDIF_IN)
CAN_H: C7.1, J1.3, R7.1, U4.7 (CANH)
CAN_L: C7.2, J1.2, R7.2, U4.6 (CANL)
CAN_SILENT: U1.27 (20_A6_TX5_LRCLK1), U4.8 (S)
CRX: C8.1, U1.30 (23_A9_CRX1_MCLK1), U4.4 (RXD)
CTX: U1.29 (22_A8_CTX1), U4.1 (TXD)
ESP_UART_RX: U1.3 (1_TX1_CTX2_MISO1), U2.8 (PB09_A7_D7_RX)
ESP_UART_TX: U1.2 (0_RX1_CRX2_CS1), U2.7 (PB08_A6_D6_TX)
GND: C1.2, C2.2, C4.2, C5.2, C6.2, C8.2, J1.4, R1.2, R2.2, R3.2, R4.2, R5.2, R6.2, U1.1 (GND), U1.17 (GND), U1.32 (GND), U2.13 (GND), U3.4 (GND), U4.2 (GND)
unnamed: C3.1, U3.6 (BST)
unnamed: D1.1 (K), R3.1
unnamed: D2.1 (K), R4.1
unnamed: D3.1 (K), R5.1
unnamed: D4.1 (K), R6.1
